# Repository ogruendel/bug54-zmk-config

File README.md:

# Bug54 keyboard
The Bug54 is a 54 key split keyboard featuring a 4x6 column staggered layout with 3 thumb keys.

I'm up to building this keyboard for people who don't want to do so themselves. Feel free to reach out to me.

## Features:
- 54 key column staggered layout
- Hotswap Kailh Choc V1 & V2
- Ultra thin: **5.7mm** for the case and **< 15mm** to the top of the keys for great portability
- Reversible PCBs for greater efficiency when ordering
- ZMK Studio Support

## Hardware
The Bug54 is designed for NiceNano V2 and compatible microcontrollers.

## Quirks / Issues / Ideas
- Currently there is only support for SOD323 Diodes
- My custom footprint for the hotswap case cutouts is non ideal and depending on your 3D Printer settings, the fit might be too tight / loose. For me they snap in with a bit of pressure, thus there is no need for screws
- It might be smart to upstream the ZMK config to the ZMK repository

## Images

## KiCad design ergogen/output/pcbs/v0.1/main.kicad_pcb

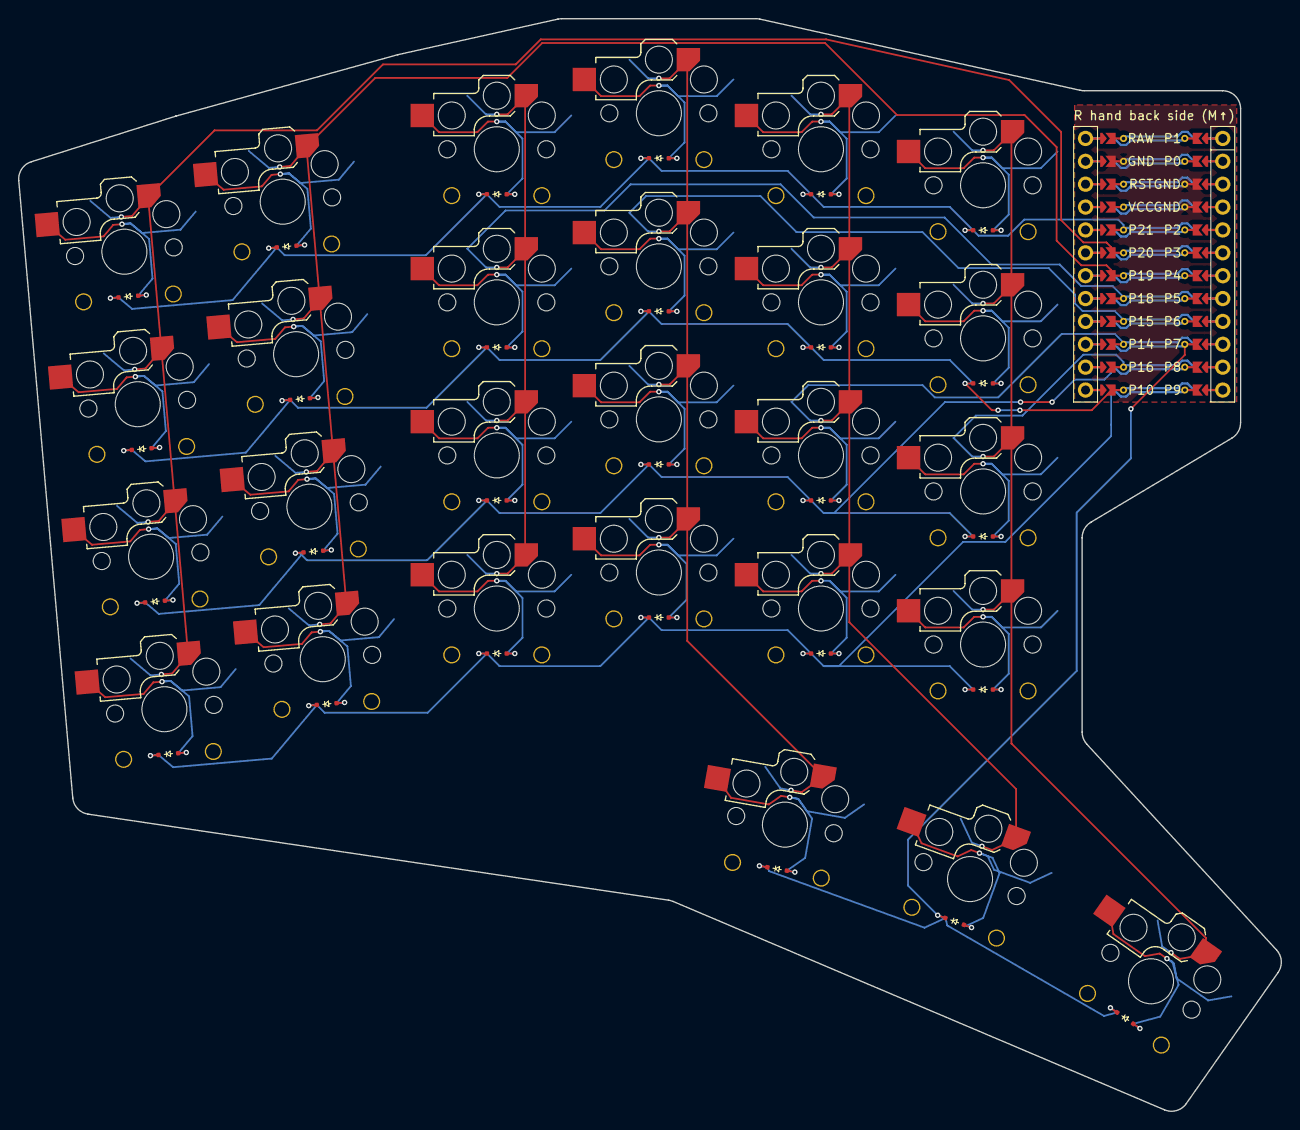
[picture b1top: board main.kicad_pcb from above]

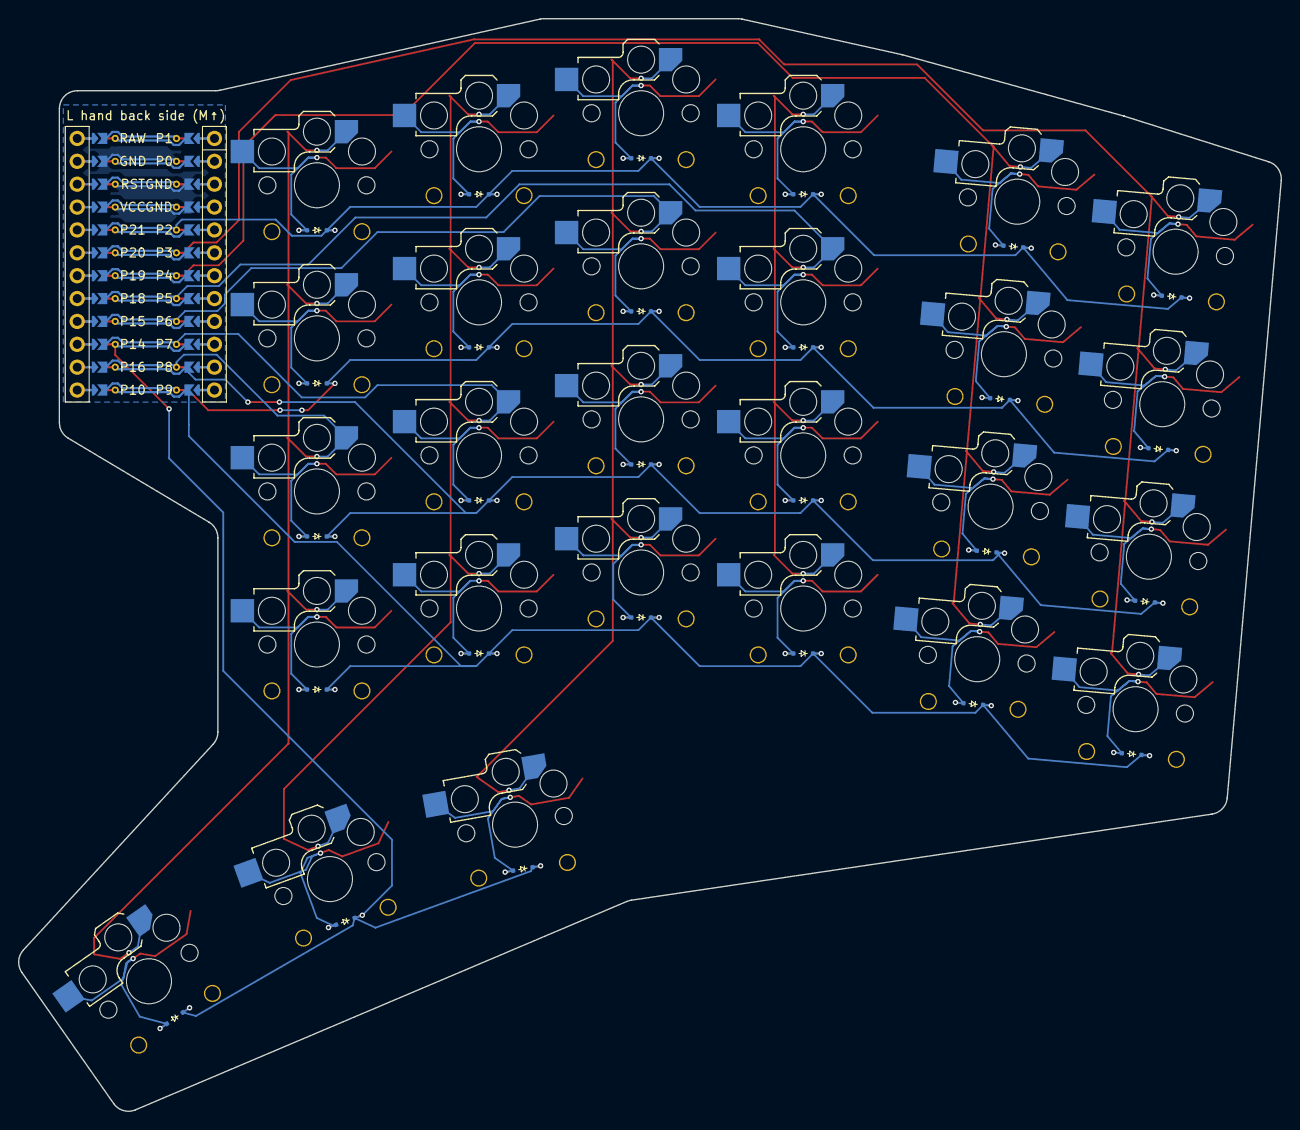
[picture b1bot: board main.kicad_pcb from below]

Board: 2 copper layers, 140.2 x 121.3 mm, 28 parts (27 on the bottom side), 7 nets.

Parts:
MCU1: mcu_nice_nano
S1, S2, S3, S4, S5, S6, S7, S8, S9, S10, S11, S12, S13, S14, S15, S16, S17, S18, S19, S20, S21, S22, S23, S24, S25, S26, S27: switch_choc_v1_v2

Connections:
GND: MCU1.103, MCU1.104, MCU1.123
P14: MCU1.115, S17.1, S18.1, S19.1, S20.1, S26.1
P15: MCU1.116, S13.1, S14.1, S15.1, S16.1, S25.1
P16: MCU1.114, S21.1, S22.1, S23.1, S24.1, S27.1
P18: MCU1.117, S9.1, S10.1, S11.1, S12.1
P19: MCU1.118, S5.1, S6.1, S7.1, S8.1
P20: MCU1.119, S1.1, S2.1, S3.1, S4.1

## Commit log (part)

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2025-04-30 Initial User Config.
2025-05-03 feat: First Layout
2025-05-03 fix: include right file
2025-05-03 fix: typo
2025-05-03 fix: add keys property support
2025-05-03 feat: add kscan0 driver
2025-05-03 fix: fix includes
2025-05-03 chore: consolidate files
2025-05-03 chore: split files to separate halves
2025-05-03 chore: change to nice_nano_v2
2025-05-03 chore: change to pro_micro
2025-05-03 feat: add second layer
2025-05-03 fix: add chosen section
2025-05-08 fix: change number and misc keys to right keycodes
2025-05-08 fix: change number keycode
2025-05-08 fix: fix right half column pins
2025-05-08 feat: preliminary symbol layout
2025-05-08 feat: add reset firmware
2025-05-08 fix: remove whitespace as per docs
2025-05-08 feat: add hardware metadata file
2025-05-08 fix: add xtal override for debugging ble connection issues
2025-05-08 debug: more debugging
2025-05-08 move config files
2025-05-08 remove old config files
2025-05-08 debug: remove debug config files
2025-05-08 feat: add zmk studio support
2025-05-08 more debugging
2025-05-09 even more debugging
2025-05-09 remove debug config files
2025-05-10 feat: rework keymap with physical mockup
2025-05-11 feat: updated keymap
2025-05-11 fix: capitalisation
2025-05-11 debug: remove second layer
2025-05-11 debug: readd second layer and reformat
2025-05-11 fix: wrong alt keycode
2025-05-15 feat: add hardware / ergogen files
2025-05-17 feat: add gitignore
2025-05-17 feat: add new hardware revision
2025-05-17 feat: update hotswap outline footprint
2025-05-17 debug
2025-05-17 undo debugging
2025-05-17 feat: add non us layout
2025-05-17 fix: update correct number keycodes
2025-05-17 feat: update case files and hotswap socket cutout footprint
2025-05-17 feat: change layout for zmk studio support
2025-05-17 fix: remove unnecessary stuff
2025-05-17 fix: add physical layout to chosen node
2025-05-18 feat: add studio unlock key
2025-05-18 feat: add readme
2025-05-18 docs: add images
2025-05-18 Create LICENSE
2025-05-19 feat: rename shield to bug54
2025-05-19 feat: update keymap
2025-05-20 feat: add support for showing battery level of both halves
2025-05-20 chore: add repo url to metadata files
2025-05-20 feat: add deep sleep support
2025-05-27 feat: add reversible reset button
2025-06-01 feat: add button footprint
2025-06-01 feat: add improved NiceNanoV2 footprint
2025-06-01 feat: add dedicated battery holes footprint
2025-06-01 feat: add slide switch footprint
2025-06-01 feat: add v0.2 main pcb
2025-06-01 chore: update README
2025-06-05 feat: update case design to fit power switch
2025-06-17 fix: update case files to fit PCB
2025-06-22 Update LICENSE
2025-07-13 change diode footprint from SOD-323F to SOD-323
2025-07-31 remove unused ceoloide footprints
2025-07-31 chore: update .gitignore
2025-08-02 feat: add attribute element to footprints
2025-08-03 feat: update socket cutout to match footprint
2026-03-07 feat: add BOM.md bill of materials
2026-03-07 fix: update build.yaml with updated mcu
2026-03-07 fix: update board variant to reflect 4.1 update
